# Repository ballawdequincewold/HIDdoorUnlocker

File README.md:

HIDdoorUnlocker
===============

Demonstration project for building a Dorm Room door unlocking mechanism that reads BuzzCards

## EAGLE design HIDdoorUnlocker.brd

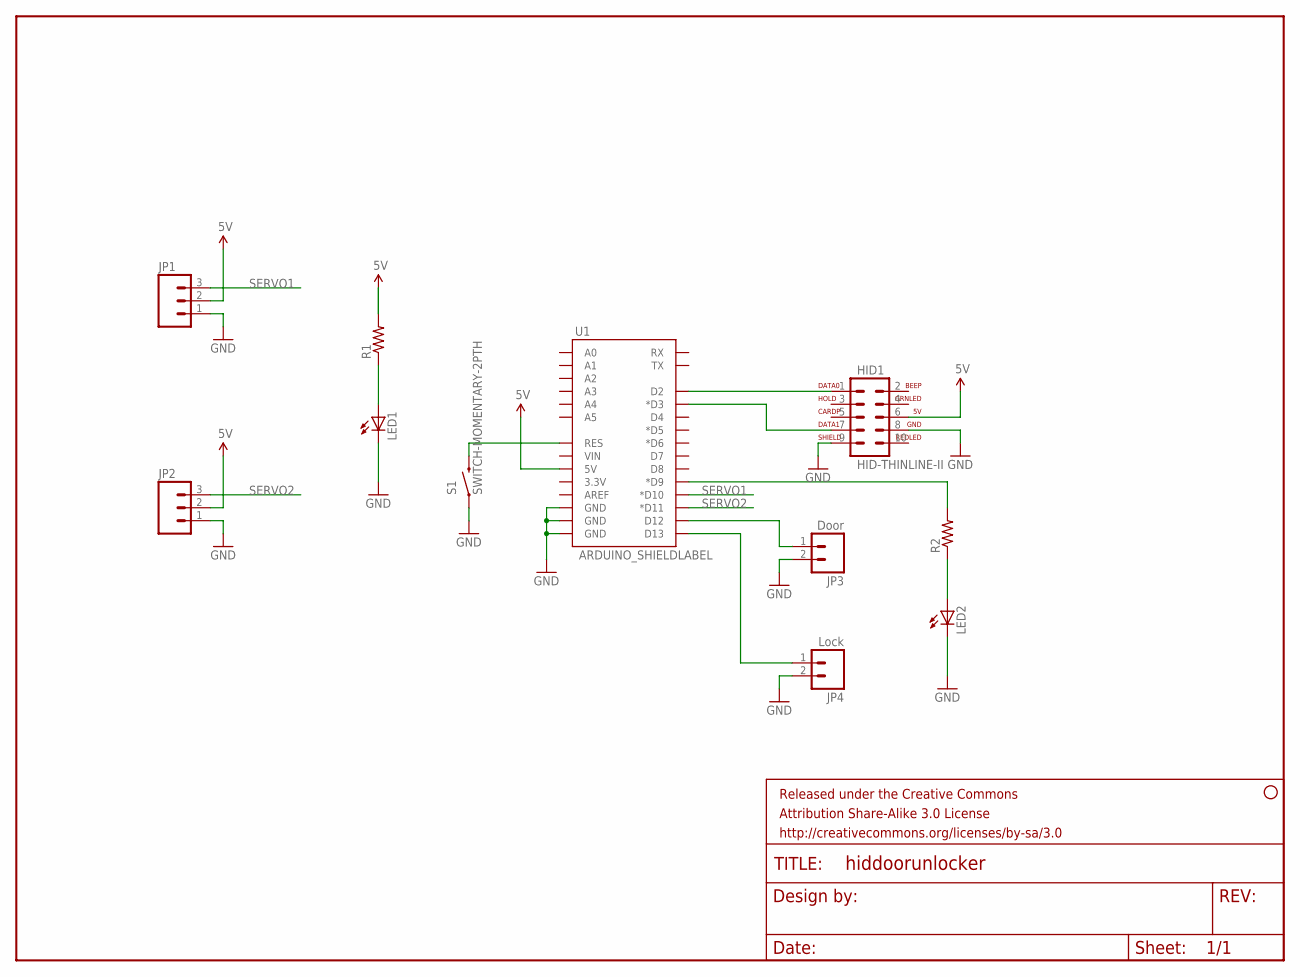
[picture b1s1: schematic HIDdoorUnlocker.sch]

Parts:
FRAME1: FRAME-LETTER; CREATIVE_COMMONS
HID1: HID-THINLINE-II; HID-2X5
JP1, JP2: M03PTH; 1X03
JP3: Door; 1X02
JP4: Lock; 1X02
LED1, LED2: LED5MM
R1, R2: RESISTORPTH-1/4W; AXIAL-0.4
S1: SWITCH-MOMENTARY-2PTH; TACTILE-PTH
STANDOFF1: STAND-OFF
U1: ARDUINO_SHIELDLABEL; DUEMILANOVE_SHIELD

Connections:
5V: HID1.6, JP1.2, JP2.2, R1.P$2 (2), U1.5V
GND: HID1.8, HID1.9, JP1.1, JP2.1, JP3.2, JP4.2, LED1.K (C), LED2.K (C), S1.1, U1.GND@0 (GND), U1.GND@1 (GND), U1.GND@2 (GND)
unnamed: LED1.A, R1.P$1 (1)
unnamed: S1.3 (2), U1.RES
unnamed: HID1.1, U1.D2
unnamed: HID1.7, U1.D3 (*D3)
unnamed: LED2.A, R2.P$1 (1)
unnamed: R2.P$2 (2), U1.D9 (*D9)
unnamed: JP3.1, U1.D12
unnamed: JP4.1, U1.D13
SERVO1: JP1.3, U1.D10 (*D10)
SERVO2: JP2.3, U1.D11 (*D11)

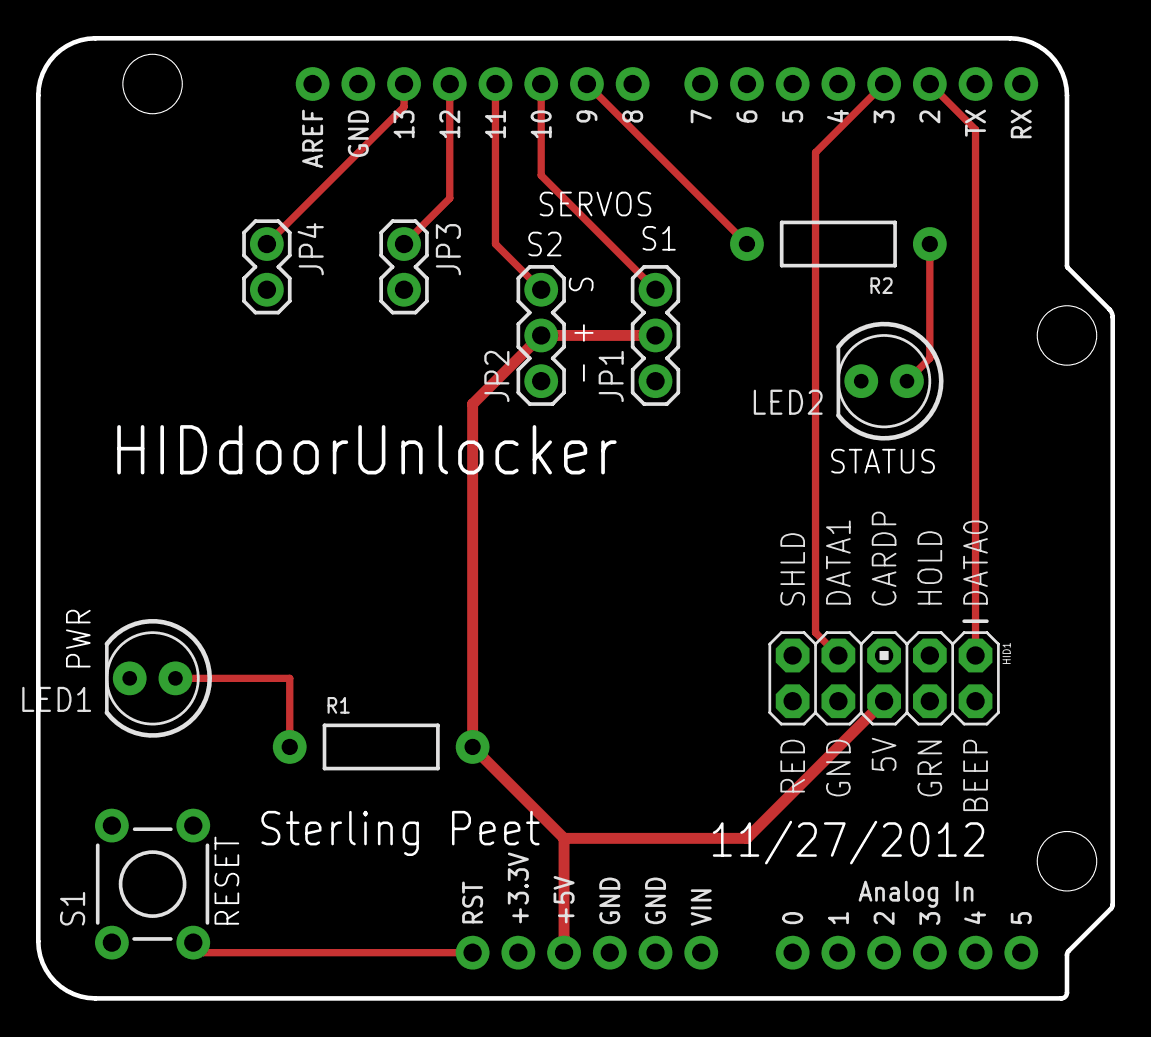
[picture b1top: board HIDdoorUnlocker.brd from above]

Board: 2 copper layers, 59.7 x 53.3 mm, 13 parts (0 on the bottom side), 12 nets.

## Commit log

2012-11-27 Add the library that contains our HID device
    This custom library contains the device with the schematic symbol and
    pcb footprint for an HID scanner's connector.
2012-11-28 Resulting files from Eagle Walkthrough Demo
    This is the files as they were presented, we will probably clean them up
    a bit if we are to use them for a physical demo.

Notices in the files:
parts and their libraries:
SparkFun-Aesthetics: Licensing: CC v3.0 Share-Alike You are welcome to use this library for commercial purposes.
SparkFun-Aesthetics: Released under the Creative Commons Attribution Share-Alike 3.0 License
SparkFun-Aesthetics: http://creativecommons.org/licenses/by-sa/3.0
